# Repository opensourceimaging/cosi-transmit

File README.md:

# cosi-transmit

COSI Transmit is an Open Source Software and Hardware project of a transmitter for 
traditional and rotating magnetic resonance imaging. The documentation for the hardware 
and the software is made freely available to the community. 

This work is part of the Open Source Imaging Initiative (www.opensourceimaging.org) and more
information on the project can be accessed here: http://www.opensourceimaging.org/project/cosi-transmit/

--------------------------

It is an ongoing project with incomplete documentation, so if you have questions please contact: 

Lukas Winter (lukas.winter@ptb.de)

--------------------------

If you find COSI Transmit useful in your work, please cite this publication:

Blücher C, Han H, Hoffmann W, Seemann R, Seifert F, Niendorf T, and Winter L,
"COSI Transmit: Open Source Soft- and Hardware Transmission System for traditional
and rotating MR", Proc ISMRM, 2017, #184

If you find grMRI useful in your work, please cite this publication:

Hasselwander, Christopher J., Zhipeng Cao, and William A. Grissom. 
"gr-MRI: A software package for magnetic resonance imaging using software defined radios." 
Journal of Magnetic Resonance 270 (2016): 47-55.

--------------------------

Documentation published describing Hardware is licensed under the CERN OHL v1.2.
For information on the license please read the DISCLAIMER.pdf

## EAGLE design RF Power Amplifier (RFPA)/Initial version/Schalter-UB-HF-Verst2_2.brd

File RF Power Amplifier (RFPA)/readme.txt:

We have too many open projects in parallel at the moment, hence the documentation of the power amp is very raw, with the next rebuild we will improve that. However we uploaded already all the schematics and some basic documentation in order to rebuild the amp. If you do build the amp it would be highly appreciated if you document the process/partlist etc so that we can upload it here (of course we will add you to the contributor list). That would really help the next users in their rebuilding process.

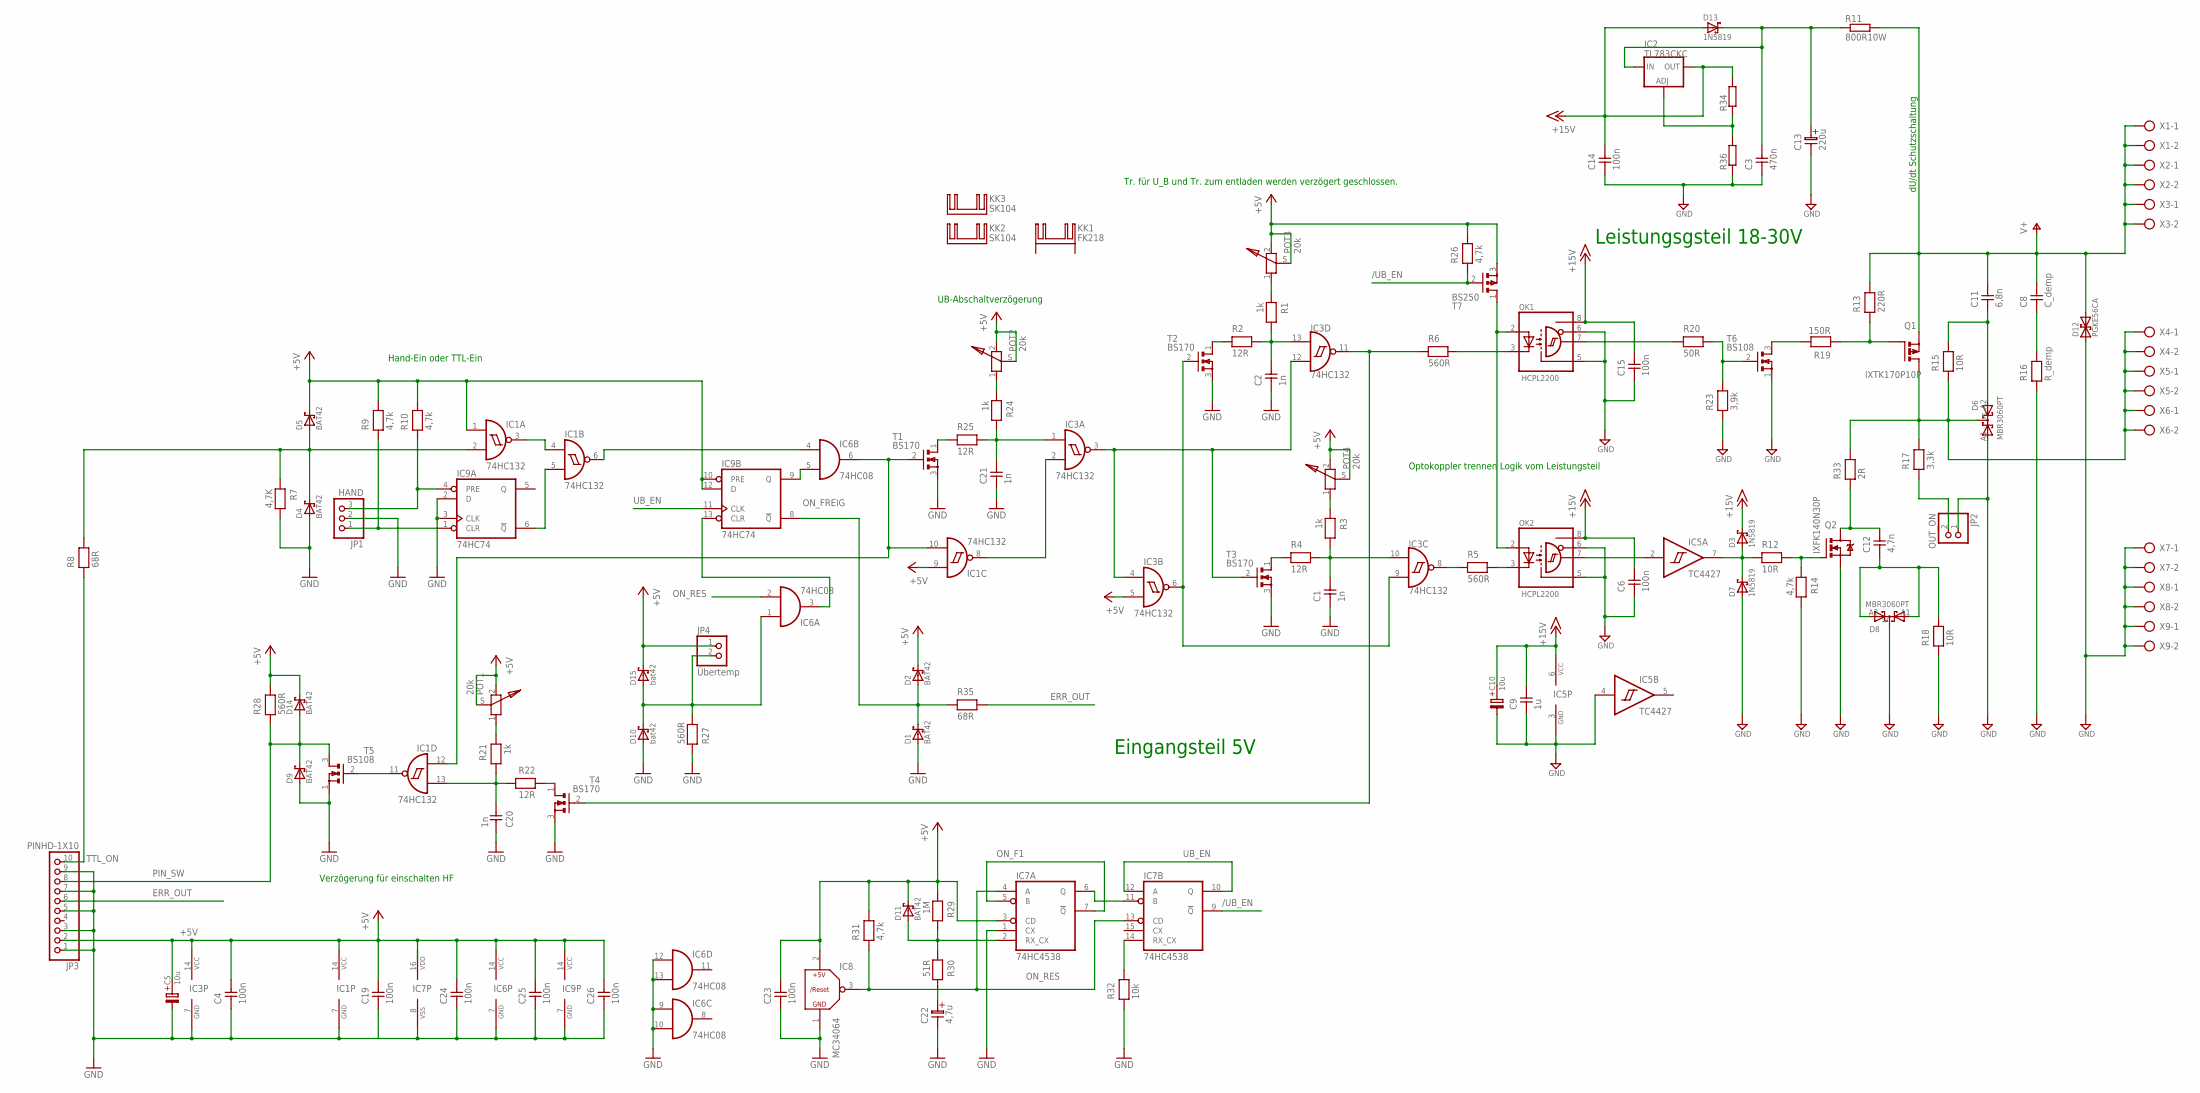
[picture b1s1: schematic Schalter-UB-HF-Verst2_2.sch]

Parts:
C1, C2, C20, C21: 1n; C-2,5
C3: 470n; C-5
C4, C6, C14, C15, C19, C23, C24, C25, C26: 100n; C-2,5
C5, C10: 10u; B45181A
C8: C_demp; C-7,5
C9: 1u; C-5
C11: 6,8n; C-10
C12: 4,7n; C-10
C13: 220u; ES-5
C22: 4,7u; ES-2,5
D1, D2, D4, D5, D9, D11, D14: BAT42; D-5
D3, D7: 1N5819; F-126-10
D6, D8: MBR3060PT; SOT93S
D10, D15: bat42; D-5
D12: PGKE56CA; CB417-15
D13: 1N5819; F126-10
IC1, IC3: 74HC132; DIL14
IC2: TL783CKC; TO220S
IC5: TC4427; DIL08
IC6: 74HC08; DIL14
IC7: 74HC4538; DIL16
IC8: MC34064; TO92
IC9: 74HC74; DIL14
JP1: HAND; 1X03
JP2: OUT_ON; 1X02
JP3: PINHD-1X10; 1X10
JP4: Übertemp; 1X02
KK1: FK218
KK2, KK3: SK104
OK1, OK2: HCPL2200; DIL08
POT1, POT2, POT3, POT4: 20k; PT-10-SI
Q1: IXTK170P10P; TO220BV
Q2: IXFK140N30P; TO247BV
R1, R3, R21, R24: 1k; R-7,5
R2, R4, R22, R25: 12R; R-7,5
R5, R6, R27, R28: 560R; R-7,5
R7: 4,7K; R-7,5
R8, R35: 68R; R-7,5
R9, R10, R14, R26: 4,7k; R-7,5
R11: 800R10W; P0817V
R12: 10R; R-7,5
R13: 220R; R25
R15, R18: 10R; R-12,5
R16: R_demp; R-12,5
R17: 3,3k; R-12,5
R19: 150R; R-12,5
R20: 50R; R-7,5
R23: 3,9k; R-7,5
R29: 1M; R-7,5
R30: 51R; R-7,5
R31: 4,7k; RS-2,5
R32: 10k; R-7,5
R33: 2R; R-TO220
R34, R36: R-EU_0204/7; 0204/7
T1, T2, T3, T4: BS170; TO-92
T5, T6: BS108; TO92-
T7: BS250; TO-92
X1, X2, X3, X4, X5, X6, X7, X8, X9: AK500/2

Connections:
+5V: C4.2, C5.+, C19.2, C23.2, C24.2, C25.2, C26.2, D2.2 (K), D5.2 (K), D11.2 (K), D14.2 (K), D15.2 (K), IC1.1 (I0), IC1.9 (I0), IC1.14 (VCC), IC3.5 (I1), IC3.14 (VCC), IC6.14 (VCC), IC7.3 (CD), IC7.16 (VDD), IC8.2 (+5V), IC9.10 (PRE), IC9.12 (D), IC9.14 (VCC), JP3.2, JP4.1, POT1.2, POT1.S (3), POT2.2, POT2.S (3), POT3.2, POT3.S (3), POT4.2, POT4.S (3), R9.2, R10.2, R26.2, R28.2, R29.1, R31.2, T7.3 (S)
+15V: C6.2, C9.2, C10.+, C14.2, C15.2, D3.K, D13.A, IC2.2 (OUT), IC5.6 (VCC), OK1.8 (VCC), OK2.8 (VCC), R34.2
/UB_EN: IC7.9 (!Q), R26.1, T7.2 (G)
ERR_OUT: JP3.6, R35.2
GND: C1.1, C2.1, C4.1, C5.-, C19.1, C20.1, C21.1, C22.2, C23.1, C24.1, C25.1, C26.1, D1.1 (A), D4.1 (A), D9.1 (A), D10.1 (A), IC1.7 (GND), IC3.7 (GND), IC6.7 (GND), IC6.9 (I0), IC6.10 (I1), IC6.12 (I0), IC6.13 (I1), IC7.1 (CX), IC7.8 (VSS), IC8.1 (GND), IC9.2 (D), IC9.3 (CLK), IC9.7 (GND), JP1.2, JP3.1, JP3.3, JP3.5, JP3.7, JP3.9, R7.2, R27.1, R32.1, T1.3 (S), T2.3 (S), T3.3 (S), T4.3 (S), T5.1 (S)
GND-PWR: C3.1, C6.1, C9.1, C10.-, C13.2, C14.1, C15.1, D6.A1, D7.A, D8.K, D12.A (1), IC5.3 (GND), IC5.4 (I), JP2.1, OK1.5 (GND), OK1.6 (VE), OK2.5 (GND), OK2.6 (VE), Q2.S, R14.2, R16.1, R18.1, R23.1, R36.1, T6.1 (S), X7.1, X7.2, X8.1, X8.2, X9.1, X9.2
HAND_OFF: IC9.4 (PRE), JP1.3, R10.1
HAND_ON: IC9.1 (CLR), JP1.1, R9.1
unnamed: C1.2, IC3.10 (I1), R3.2, R4.2
unnamed: IC3.6 (O), IC3.9 (I0), T2.2 (G)
unnamed: R2.1, T2.1 (D)
unnamed: C2.2, IC3.13 (I1), R1.2, R2.2
unnamed: IC1.3 (O), IC1.4 (I0)
unnamed: IC6.3 (O), IC9.13 (CLR)
unnamed: R4.1, T3.1 (D)
unnamed: IC2.1 (ADJ), R34.1, R36.2
unnamed: OK1.3 (K), R6.2
unnamed: IC3.11 (O), R6.1, T4.2 (G)
unnamed: OK2.3 (K), R5.2
unnamed: IC3.8 (O), R5.1
unnamed: D3.A, D7.K, IC5.7 (O), R12.1
unnamed: D1.2 (K), D2.1 (A), IC9.8 (!Q), R35.1
unnamed: D4.2 (K), D5.1 (A), IC1.2 (I1), R7.1, R8.2
unnamed: IC1.6 (O), IC6.4 (I0)
unnamed: Q2.G, R12.2, R14.1
unnamed: C8.1, R16.2
unnamed: JP2.2, R17.1
unnamed: POT3.1, R1.1
unnamed: IC1.11 (O), T5.2 (G)
unnamed: R20.2, R23.2, T6.2 (G)
unnamed: IC5.2 (I), OK2.7 (VO)
unnamed: C20.2, IC1.13 (I1), R21.2, R22.2
unnamed: Q1.G, R13.1, R19.1
unnamed: C11.1, D6.A2, R15.2
unnamed: R19.2, T6.3 (D)
unnamed: C12.2, Q2.D, R33.1
unnamed: POT4.1, R3.1
unnamed: C12.1, D8.A1, D8.A2, R18.2
unnamed: IC1.8 (O), IC3.2 (I1)
unnamed: IC3.3 (O), IC3.4 (I0), IC3.12 (I0), T3.2 (G)
unnamed: IC1.5 (I1), IC9.6 (!Q)
unnamed: IC1.10 (I1), IC1.12 (I0), IC6.6 (O), T1.2 (G)
unnamed: R22.1, T4.1 (D)
unnamed: OK1.7 (VO), R20.1
unnamed: POT2.1, R24.1
unnamed: C21.2, IC3.1 (I0), R24.2, R25.2
unnamed: R25.1, T1.1 (D)
unnamed: IC7.6 (Q), IC7.11 (B)
unnamed: OK1.2 (A), OK2.2 (A), T7.1 (D)
unnamed: POT1.1, R21.1
unnamed: C22.1, R30.2
unnamed: D11.1 (A), IC7.2 (RX_CX), R29.2, R30.1
unnamed: IC7.14 (RX_CX), R32.2
ON_F1: IC7.5 (B), IC7.7 (!Q)
ON_FREIG: IC6.5 (I1), IC9.9 (Q)
ON_RES: IC6.2 (I1), IC7.4 (A), IC7.13 (CD), IC8.3 (/RESET), R31.1
OUT: D6.K, Q1.S, R15.1, R17.2, R33.2, X4.1, X4.2, X5.1, X5.2, X6.1, X6.2
PIN_SW: D9.2 (K), D14.1 (A), JP3.8, R28.1, T5.3 (D)
TEMP_OFF: D10.2 (K), D15.1 (A), IC6.1 (I0), JP4.2, R27.2
TTL_ON: JP3.10, R8.1
UB_EN: IC7.10 (Q), IC7.12 (A), IC9.11 (CLK)
V+: C8.2, C11.2, D12.K (2), Q1.D, R11.2, R13.2, X1.1, X1.2, X2.1, X2.2, X3.1, X3.2
V+_1: C3.2, C13.1, D13.K, IC2.3 (IN), R11.1

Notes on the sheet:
dU/dt Schutzschaltung
Eingangsteil 5V
Hand-Ein oder TTL-Ein
UB-Abschaltverzögerung
Verzögerung für einschalten HF
Optokoppler trennen Logik vom Leistungsteil
Leistungsgsteil 18-30V
Tr. für U_B und Tr. zum entladen werden verzögert geschlossen.

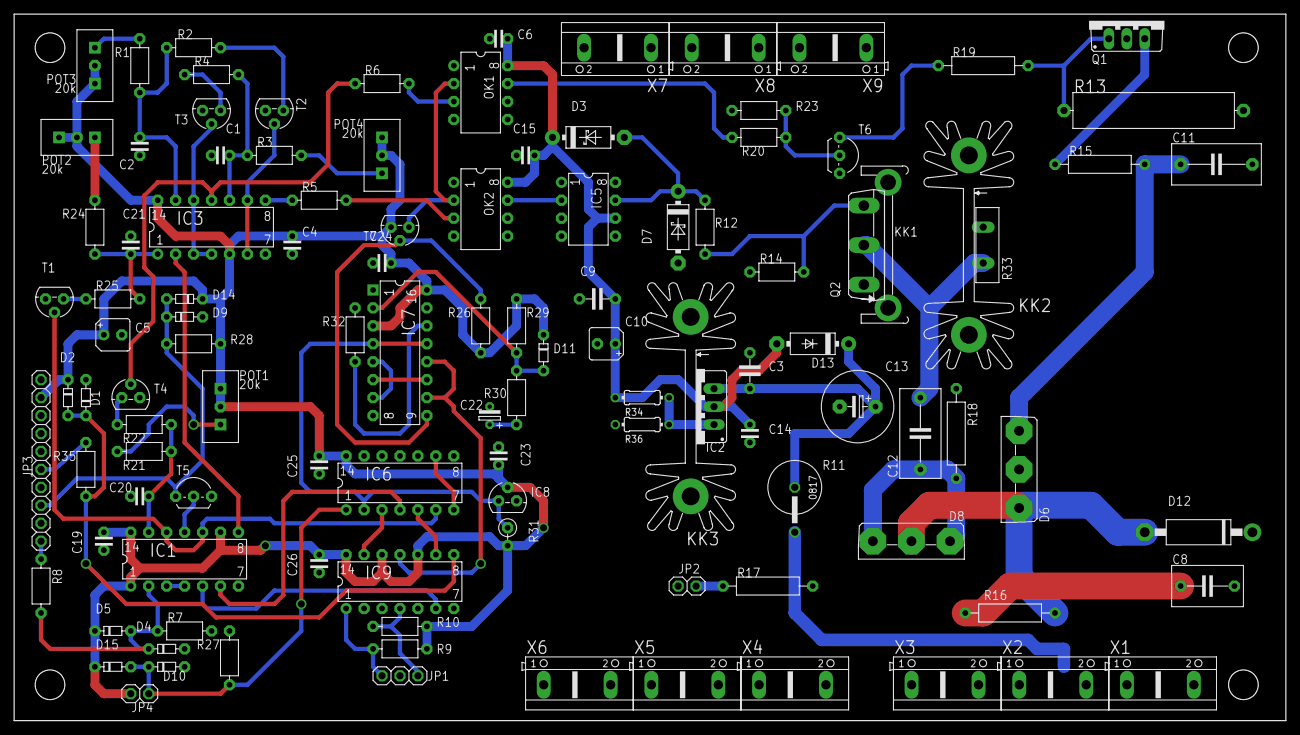
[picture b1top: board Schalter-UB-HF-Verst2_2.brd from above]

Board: 2 copper layers, 180.0 x 100.0 mm, 112 parts (0 on the bottom side), 63 nets.

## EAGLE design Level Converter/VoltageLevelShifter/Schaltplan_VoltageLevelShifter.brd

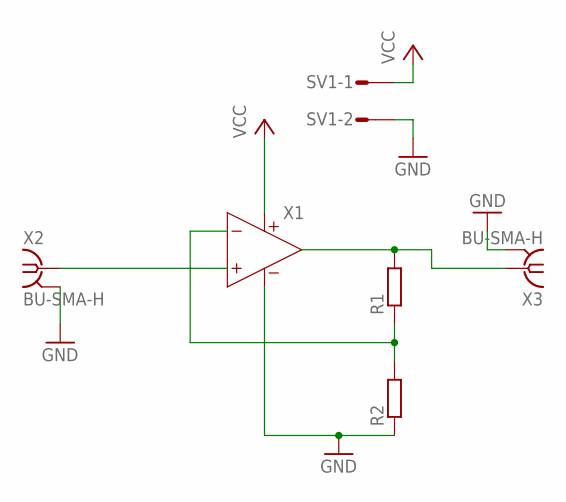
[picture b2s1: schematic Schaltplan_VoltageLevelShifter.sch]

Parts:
R1, R2: R-EU_0204/7; 0204/7
SV1: S02P
X1: UNIVERSALOPAMP2; S8
X2, X3: BU-SMA-H

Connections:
GND: R2.1, SV1.2, X1.4 (V-), X2.2, X2.3 (2), X2.4 (2), X2.5 (2), X3.2, X3.3 (2), X3.4 (2), X3.5 (2)
unnamed: X1.1 (IN+), X2.1
unnamed: R1.2, X1.3 (OUT), X3.1
unnamed: R1.1, R2.2, X1.2 (IN-)
VCC: SV1.1, X1.8 (V+)

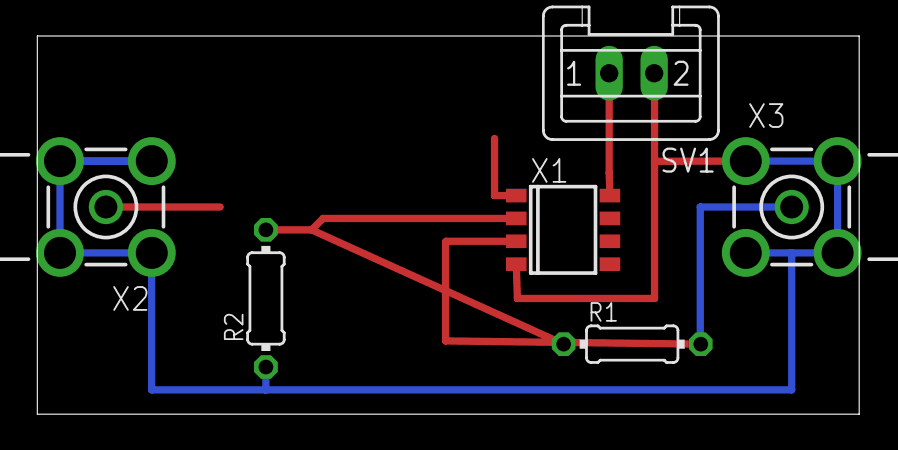
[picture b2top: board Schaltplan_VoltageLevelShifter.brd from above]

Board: 2 copper layers, 45.7 x 21.0 mm, 6 parts (0 on the bottom side), 5 nets.

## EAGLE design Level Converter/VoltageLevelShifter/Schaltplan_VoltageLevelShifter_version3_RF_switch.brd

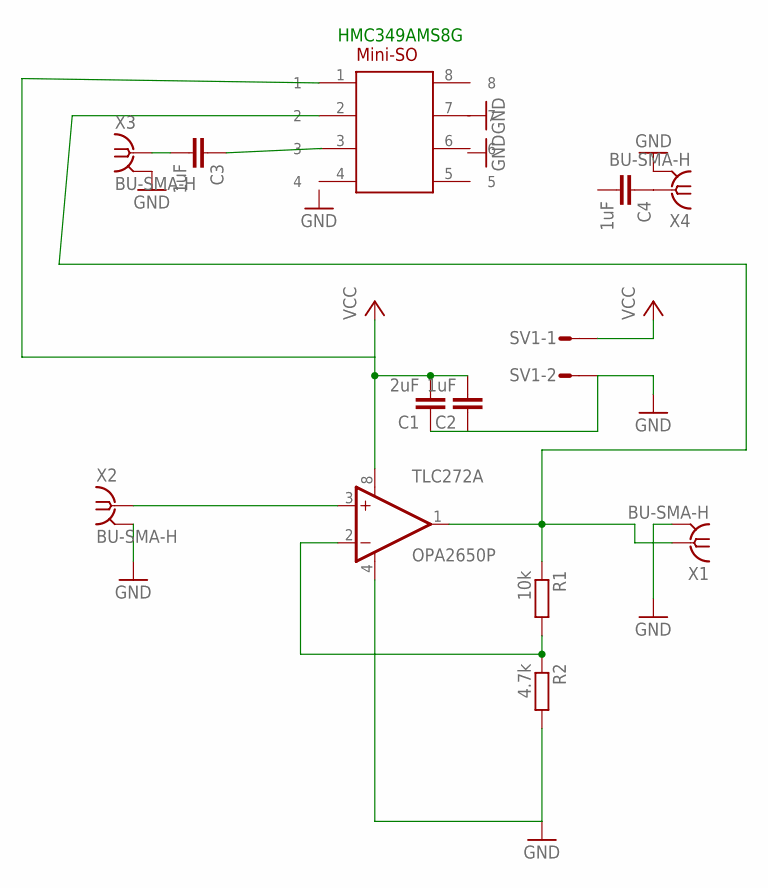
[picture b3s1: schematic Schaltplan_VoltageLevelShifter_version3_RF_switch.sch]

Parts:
C1: 2uF; YC7B5
C2, C3, C4: 1uF; YC7B5
HMC349AMS8G: MINI-SO
R1: 10k; 0207/12
R2: 4.7k; 0207/12
SV1: S02P
TLC272: OPA2650P; DIL08
X1, X2, X3, X4: BU-SMA-H

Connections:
GND: C1.1, C2.1, R2.2, SV1.2, TLC272.4 (V-), X1.2, X1.3 (2), X1.4 (2), X1.5 (2), X2.2, X2.3 (2), X2.4 (2), X2.5 (2), X3.2, X3.3 (2), X3.4 (2), X3.5 (2), X4.2, X4.3 (2), X4.4 (2), X4.5 (2)
unnamed: R1.2, R2.1, TLC272.2 (-IN)
unnamed: R1.1, TLC272.1 (OUT), X1.1
unnamed: C3.2, X3.1
unnamed: C4.1, X4.1
unnamed: TLC272.3 (+IN), X2.1
VCC: C1.2, C2.2, SV1.1, TLC272.8 (V+)

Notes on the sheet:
HMC349AMS8G

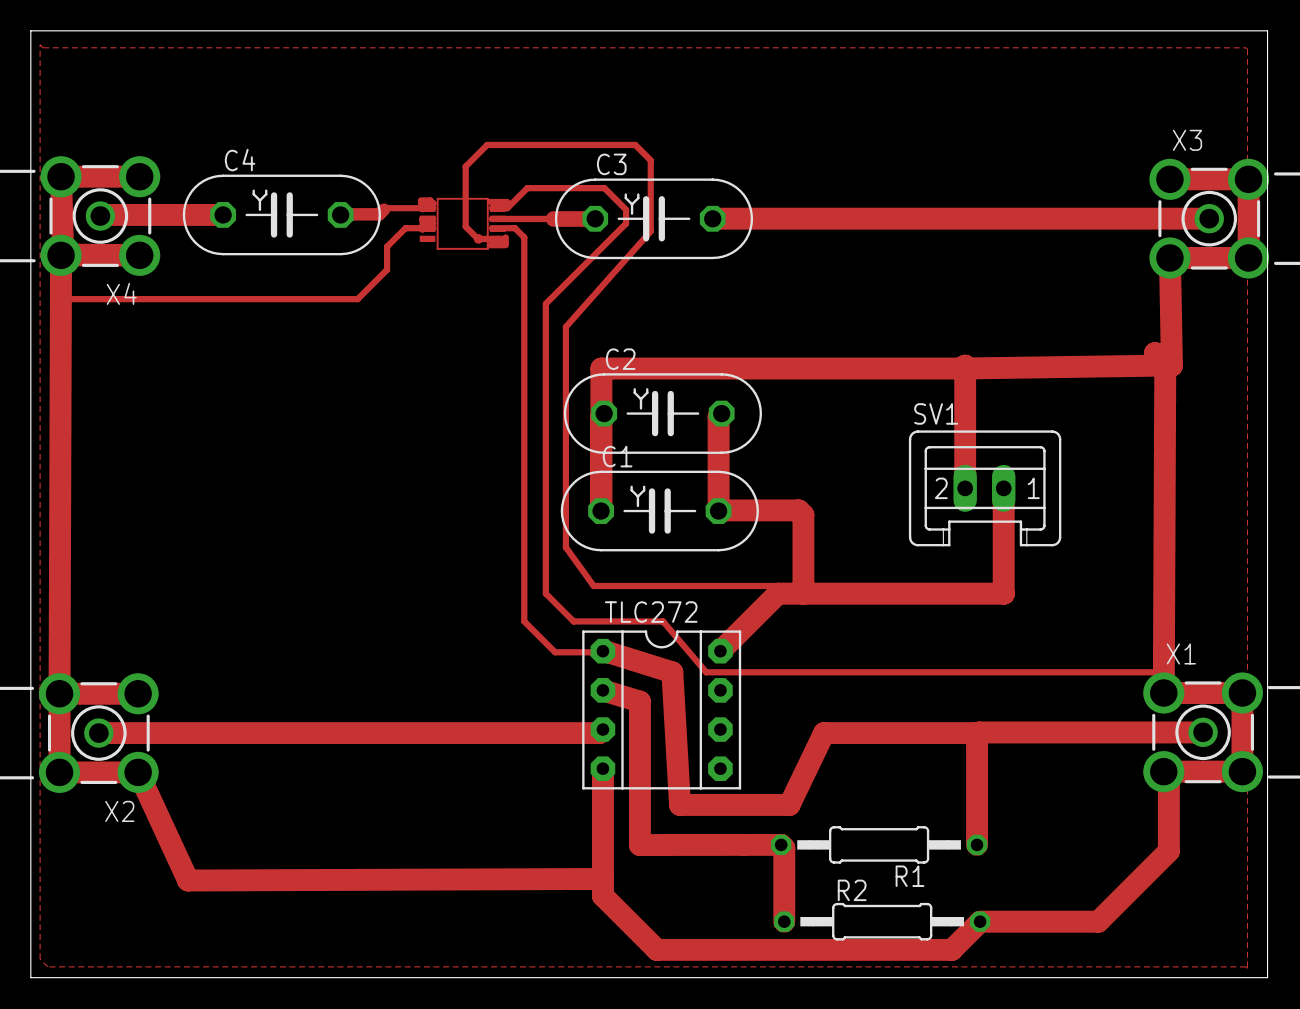
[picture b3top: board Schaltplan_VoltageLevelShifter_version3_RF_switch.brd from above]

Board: 2 copper layers, 80.2 x 61.4 mm, 13 parts (0 on the bottom side), 7 nets.

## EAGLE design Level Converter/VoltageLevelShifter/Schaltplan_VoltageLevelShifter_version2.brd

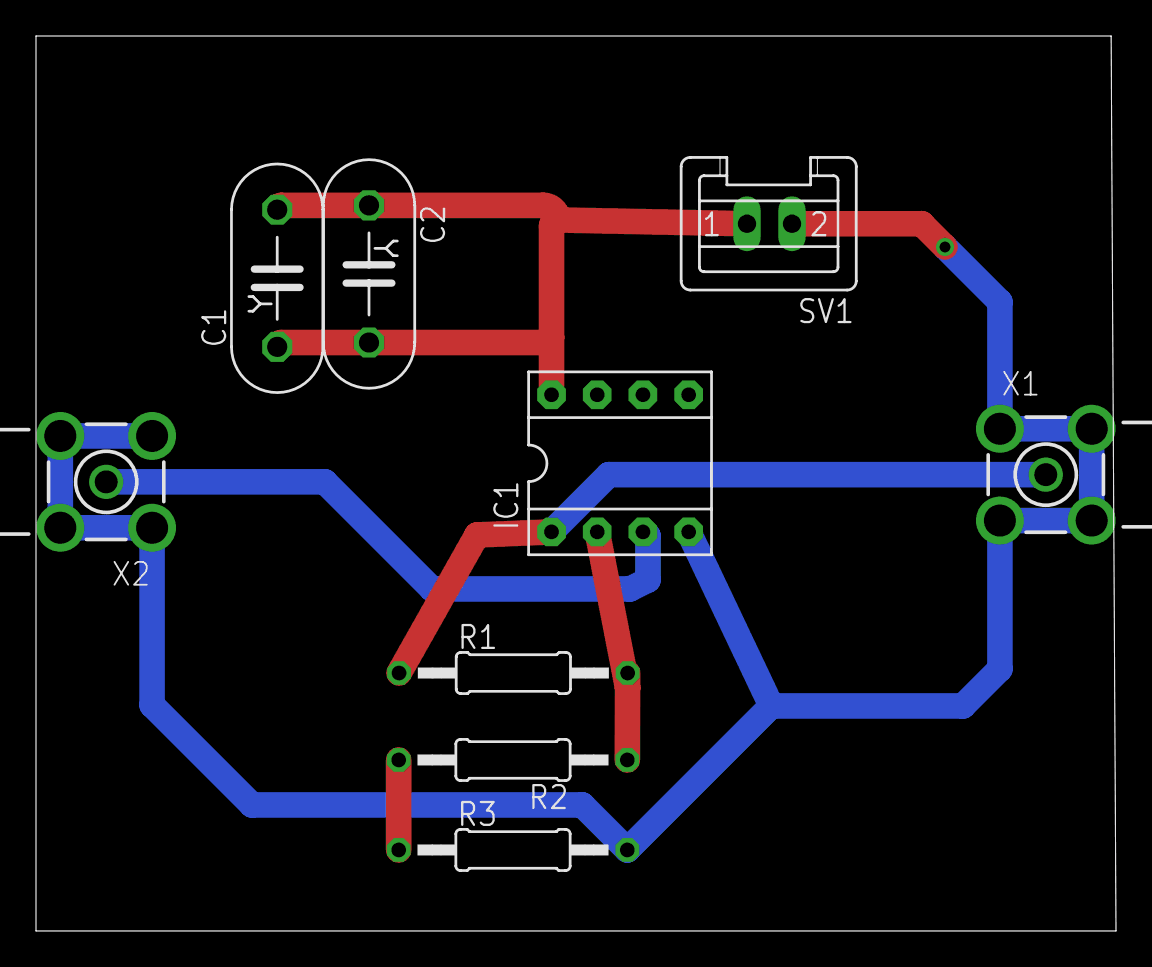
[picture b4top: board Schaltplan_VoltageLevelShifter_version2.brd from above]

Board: 2 copper layers, 60.0 x 49.7 mm, 9 parts (0 on the bottom side), 6 nets.

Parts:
C1, C2: YC7B5
IC1: OPA2650P; DIL08
R1, R2, R3: 0207/12
SV1: S02P
X1, X2: BU-SMA-H

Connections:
GND: IC1.4, R3.2, SV1.2, X1.2, X1.3, X1.4, X1.5, X2.2, X2.3, X2.4, X2.5
unnamed: IC1.2, R1.2, R2.1
unnamed: R2.2, R3.1
unnamed: IC1.1, R1.1, X1.1
unnamed: IC1.3, X2.1
VCC: C1.1, C1.2, C2.1, C2.2, IC1.8, SV1.1

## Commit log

2019-03-21 Photos/figures added
2019-05-23 added some basic RFPA documentation
2019-05-23 additional RFPA documentation files
2019-06-28 added driver document (german only)
